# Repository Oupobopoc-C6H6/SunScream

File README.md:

# SunScream — UV Monitoring and Sunscreen Analysis

SunScream is a UV-sensing project developed in two independent implementations for engineering coursework at the University of South Florida. Both use a GUVA-series ultraviolet sensor, but differ in their microcontroller, communication interface, and intended application.

The project explores embedded sensor acquisition, UV measurement and analysis, hardware design, and wired versus wireless communication. **These are two separate hardware/firmware designs**, not modes of a single device.

## Implementations

| | ESP32 UV Exposure Monitor | ATmega328P Sunscreen Analyzer |
| --- | --- | --- |
| Platform | ESP32-WROOM-32 | ATmega328P |
| Interface | Bluetooth serial to Android phone | Serial link to Python desktop GUI |
| Main function | Estimate and accumulate UV exposure; sound a threshold alert | Compare baseline and sunscreen-test UV measurements |
| Additional work | Outdoor sensor characterization, enclosure, circuit design | Desktop GUI and measurement workflow |
| Project details | [ESP32 implementation](esp32-exposure-monitor/README.md) | [ATmega328P implementation](atmega328p-sunscreen-analyzer/) |

### ESP32 — Wireless UV Exposure Monitor

This implementation combines a GUVA-S12SD UV sensor, an analog interface, an ESP32-WROOM-32, and a buzzer. The firmware samples the sensor, estimates UV exposure using an empirical relationship, and sends readings to an Android Bluetooth serial terminal. An audible alert activates when the accumulated estimate exceeds the firmware's experimental threshold.

Outdoor characterization compared ESP32 ADC readings with reported UV Index values. The team report includes the test methodology, regression analysis, results, limitations, enclosure design, and individual author contributions.

**[Explore the ESP32 implementation](esp32-exposure-monitor/README.md)** · **[Read the technical report](esp32-exposure-monitor/docs/SunScream.pdf)**

### ATmega328P — Desktop Sunscreen Analyzer

This separately developed version uses an ATmega328P to acquire UV sensor measurements and communicate with a Python/Tkinter GUI over serial. The GUI takes a baseline measurement, accepts a second measurement with a sunscreen-treated sample, and displays the relative reduction in measured UV response.

The software's percentage reduction is **not a validated SPF measurement**.

**[Explore the ATmega328P implementation](atmega328p-sunscreen-analyzer/)** · **[Python GUI instructions](atmega328p-sunscreen-analyzer/python-gui/README.md)**

## Repository layout

```text
SunScream/
├── README.md
├── atmega328p-sunscreen-analyzer/
│   ├── python-gui/
│   ├── UV_Sensor_Firmware/
│   ├── UV_Sensor_PCB/
│   └── ...
└── esp32-exposure-monitor/
    ├── CAD/
    ├── SunScreamFirmware/
    ├── SunScreamSchematic/
    ├── docs/
    │   └── SunScream.pdf
    └── README.md
```

The layout above uses the existing directory names where known. The two applications can be explored independently.

## Notes on interpretation

SunScream is an educational engineering prototype, **not a calibrated UV dosimeter or medical safety device**. Its UV Index estimates depend on the calibration setup and sensor behavior. The ESP32 report discusses high measurement variability and limited response at low reported UV Index values. The sunscreen comparison is a relative measurement and should not be presented as a certified SPF test.

## Attribution

The ESP32 work and its technical report were completed by **J. A. Groom, A. T. Carr, and C. C. Harmon**. See the [report](esp32-exposure-monitor/docs/SunScream.pdf) for the team members' individual contributions. The ATmega328P implementation was developed separately for embedded systems coursework with Sophia Alonso and Audrey Gabbard.

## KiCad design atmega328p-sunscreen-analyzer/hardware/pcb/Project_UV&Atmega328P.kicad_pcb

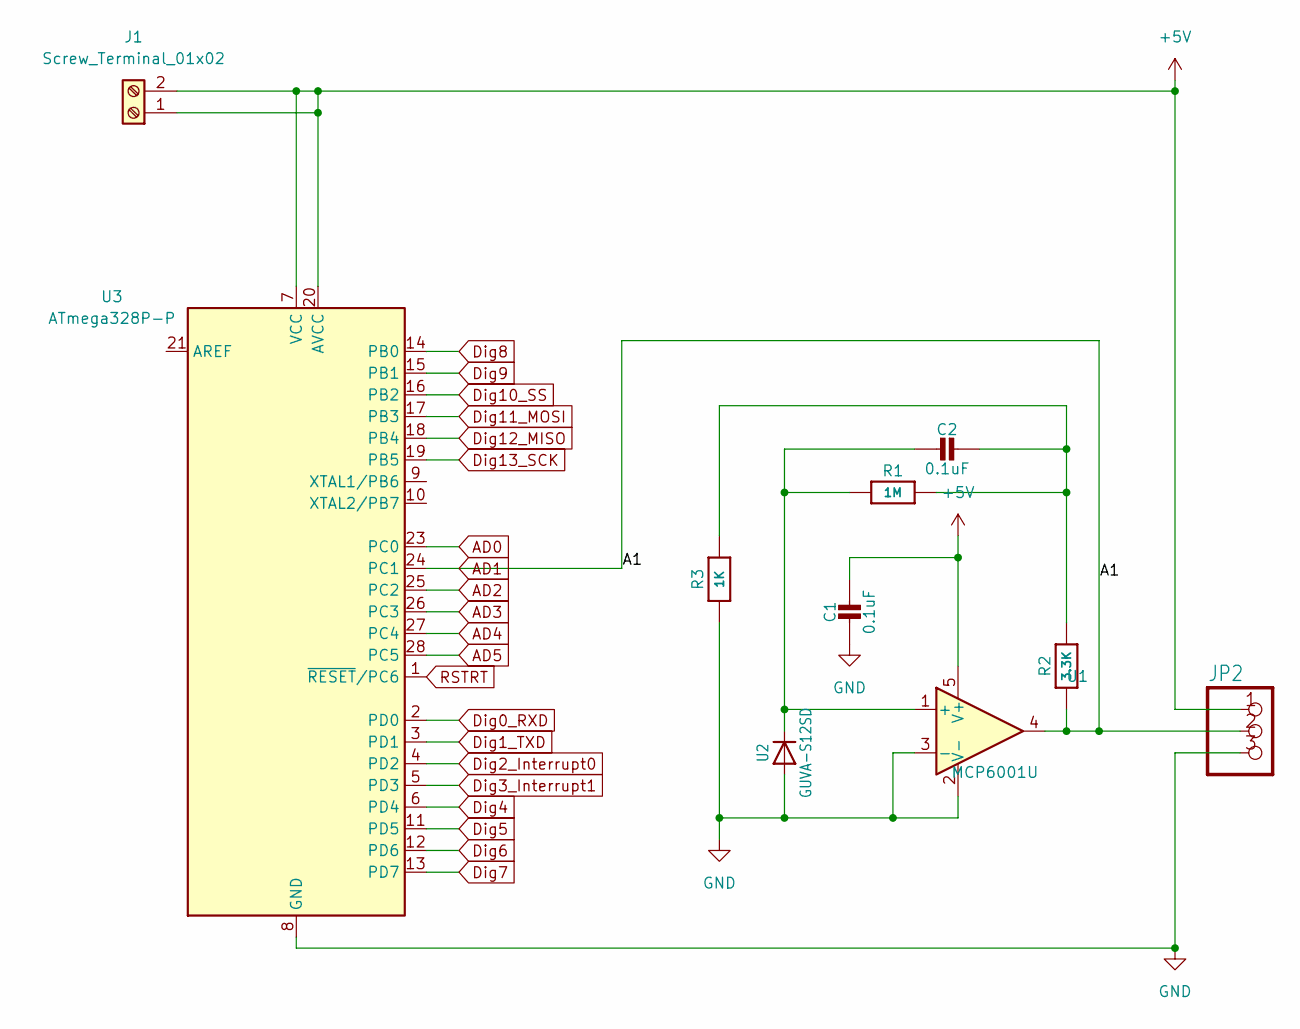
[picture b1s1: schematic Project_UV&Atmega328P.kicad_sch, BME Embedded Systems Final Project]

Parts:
C1, C2: 0.1uF; C_0805_2012Metric_Pad1.18x1.45mm_HandSolder
J1: Screw_Terminal_01x02; TerminalBlock_MaiXu_MX126-5.0-02P_1x02_P5.00mm
JP2: PINHD-1X3CB; TerminalBlock_MaiXu_MX126-5.0-03P_1x03_P5.00mm
R1: 1M; R_0805_2012Metric_Pad1.20x1.40mm_HandSolder
R2: 3.3K; R_0805_2012Metric_Pad1.20x1.40mm_HandSolder
R3: 1K; R_0805_2012Metric_Pad1.20x1.40mm_HandSolder
U1: MCP6001U; SOT-23-5_HandSoldering
U2: GUVA-S12SD; CR_GUVA-S12SD_GCM
U3: ATmega328P-P; DIP-28_W7.62mm

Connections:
+5V: C1.1, J1.1, J1.2, JP2.1, U1.5 (V+), U3.7 (VCC), U3.20 (AVCC)
AD0: U3.23 (PC0)
AD1: JP2.2, R2.1, U1.4, U3.24 (PC1)
AD2: U3.25 (PC2)
AD3: U3.26 (PC3)
AD4: U3.27 (PC4)
AD5: U3.28 (PC5)
Dig0_RXD: U3.2 (PD0)
Dig1_TXD: U3.3 (PD1)
Dig2_Interrupt0: U3.4 (PD2)
Dig3_Interrupt1: U3.5 (PD3)
Dig4: U3.6 (PD4)
Dig5: U3.11 (PD5)
Dig6: U3.12 (PD6)
Dig7: U3.13 (PD7)
Dig8: U3.14 (PB0)
Dig9: U3.15 (PB1)
Dig10_SS: U3.16 (PB2)
Dig11_MOSI: U3.17 (PB3)
Dig12_MISO: U3.18 (PB4)
Dig13_SCK: U3.19 (PB5)
GND: C1.2, JP2.3, R3.1, U1.2 (V-), U1.3 (-), U2.2 (A), U3.8 (GND), U3.22 (GND)
unnamed: C2.1, R1.2, R2.2, R3.2
unnamed: C2.2, R1.1, U1.1 (+), U2.1 (C)
RSTRT: U3.1 (~RESET/PC6)

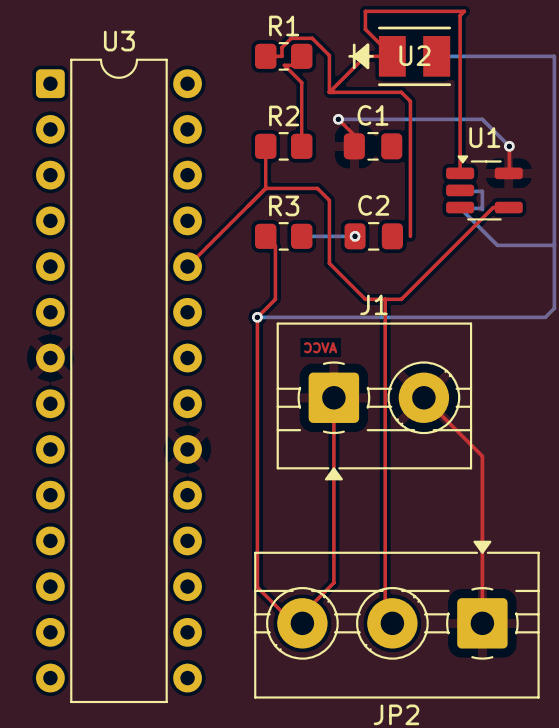
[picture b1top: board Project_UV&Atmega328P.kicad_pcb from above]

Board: 2 copper layers, 10 parts (0 on the bottom side), 5 nets.

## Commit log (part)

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2025-04-09 Created Arduino Folder/Code
    Created the main code for the arduino running the UV sensor
2025-04-09 Update SunScream_Arduino.ino
    Started Serial Communication
2025-04-14 Update SunScream_Arduino.ino
    Added an averaging function as well as boxes for index values.
2025-04-29 Test
2025-05-07 Changed schematic size
2025-05-08 Added CAD and renamed folders
